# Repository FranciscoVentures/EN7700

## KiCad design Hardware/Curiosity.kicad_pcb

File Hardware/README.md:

Intro
=======

Curiosity™ EN7700
Developed by Francisco Ventures™

Based on the open source hardware project USB Armory MK II | https://github.com/f-secure-foundry/usbarmory/tree/master/hardware/mark-two

DISCLAIMER
=======

Francisco Ventures™ (“Francisco”) is not responsible for typographical or other errors or omissions or for direct, indirect, incidental or consequential damages related to this material or resulting from its use. Francisco makes no warranty or representation respecting this material, which is provided on an "AS IS" basis. FRANCISCO HEREBY DISCLAIMS ALL WARRANTIES OR LIABILITY OF ANY KIND WITH RESPECT THERETO, INCLUDING, WITHOUT LIMITATION, REPRESENTATIONS REGARDING ACCURACY AND COMPLETENESS, ALL IMPLIED WARRANTIES AND CONDITIONS OF MERCHANTABILITY, SUITABILITY OR FITNESS FOR A PARTICULAR PURPOSE, TITLE AND/OR NON-INFRINGEMENT. This material is not designed, intended or authorized for use in medical, life support, life sustaining or nuclear applications or applications in which the failure of the product could result in personal injury, death or property damage. Any party using or selling products for use in any such applications do so at their sole risk and agree that Francisco is not liable, in whole or in part, for any claim or damage arising from such use, and agree to fully indemnify, defend and hold harmless Francisco from and against any and all claims, damages, loss, cost, expense or liability arising out of or in connection with the use or performance of products in such applications.

License
=======

This is an open hardware design licensed under the terms of the CERN Open
Hardware Licence (OHL) v1.2.

You may redistribute and modify this documentation under the terms of the CERN
OHL v.1.2 (http://ohwr.org/cernohl). This documentation is distributed WITHOUT
ANY EXPRESS OR IMPLIED WARRANTY, INCLUDING OF MERCHANTABILITY, SATISFACTORY
QUALITY AND FITNESS FOR A PARTICULAR PURPOSE. Please see the CERN OHL v.1.2 for
applicable conditions.

The following exceptions apply:

- ../lib.snapeda: all files in this directory are imported or modified
from SnapEDA symbols and footprints, therefore the license at
https://www.snapeda.com/about/FAQ/#license applies.

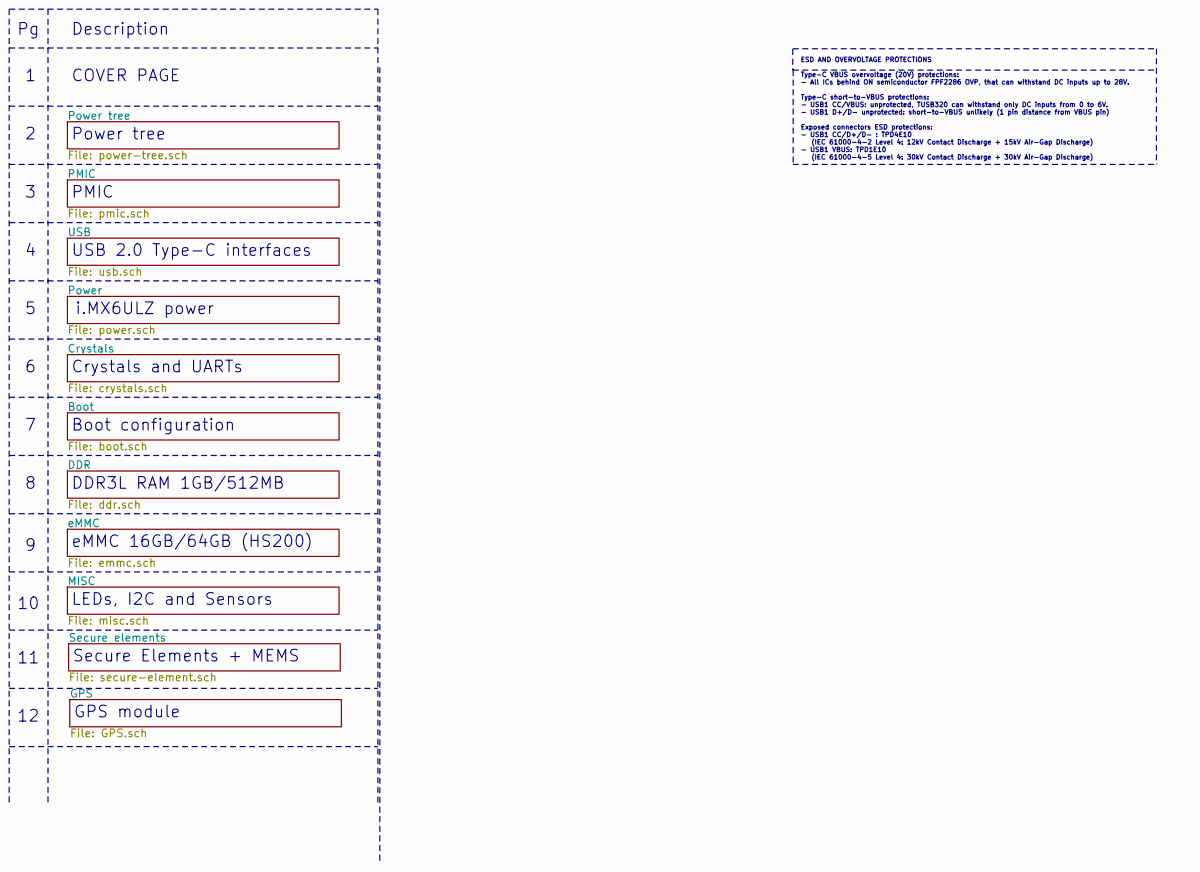
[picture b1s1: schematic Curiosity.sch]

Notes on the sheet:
DDR3L RAM 1GB/512MB
eMMC 16GB/64GB (HS200)
Secure Elements + MEMS
GPS module
Boot configuration
i.MX6ULZ power
USB 2.0 Type-C interfaces
Crystals and UARTs
ESD AND OVERVOLTAGE PROTECTIONS Type-C VBUS overvoltage (20V) protections: - All ICs behind ON semiconductor FPF2286 OVP, that can withstand DC inputs up to 28V. Type-C short-to-VBUS protections: - USB1 CC/VBUS: unprotected, TUSB320 can withstand only DC inputs from 0 to 6V. - USB1 D+/D- unprotecte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
PMIC
Description
Power tree
COVER PAGE
LEDs, I2C and Sensors

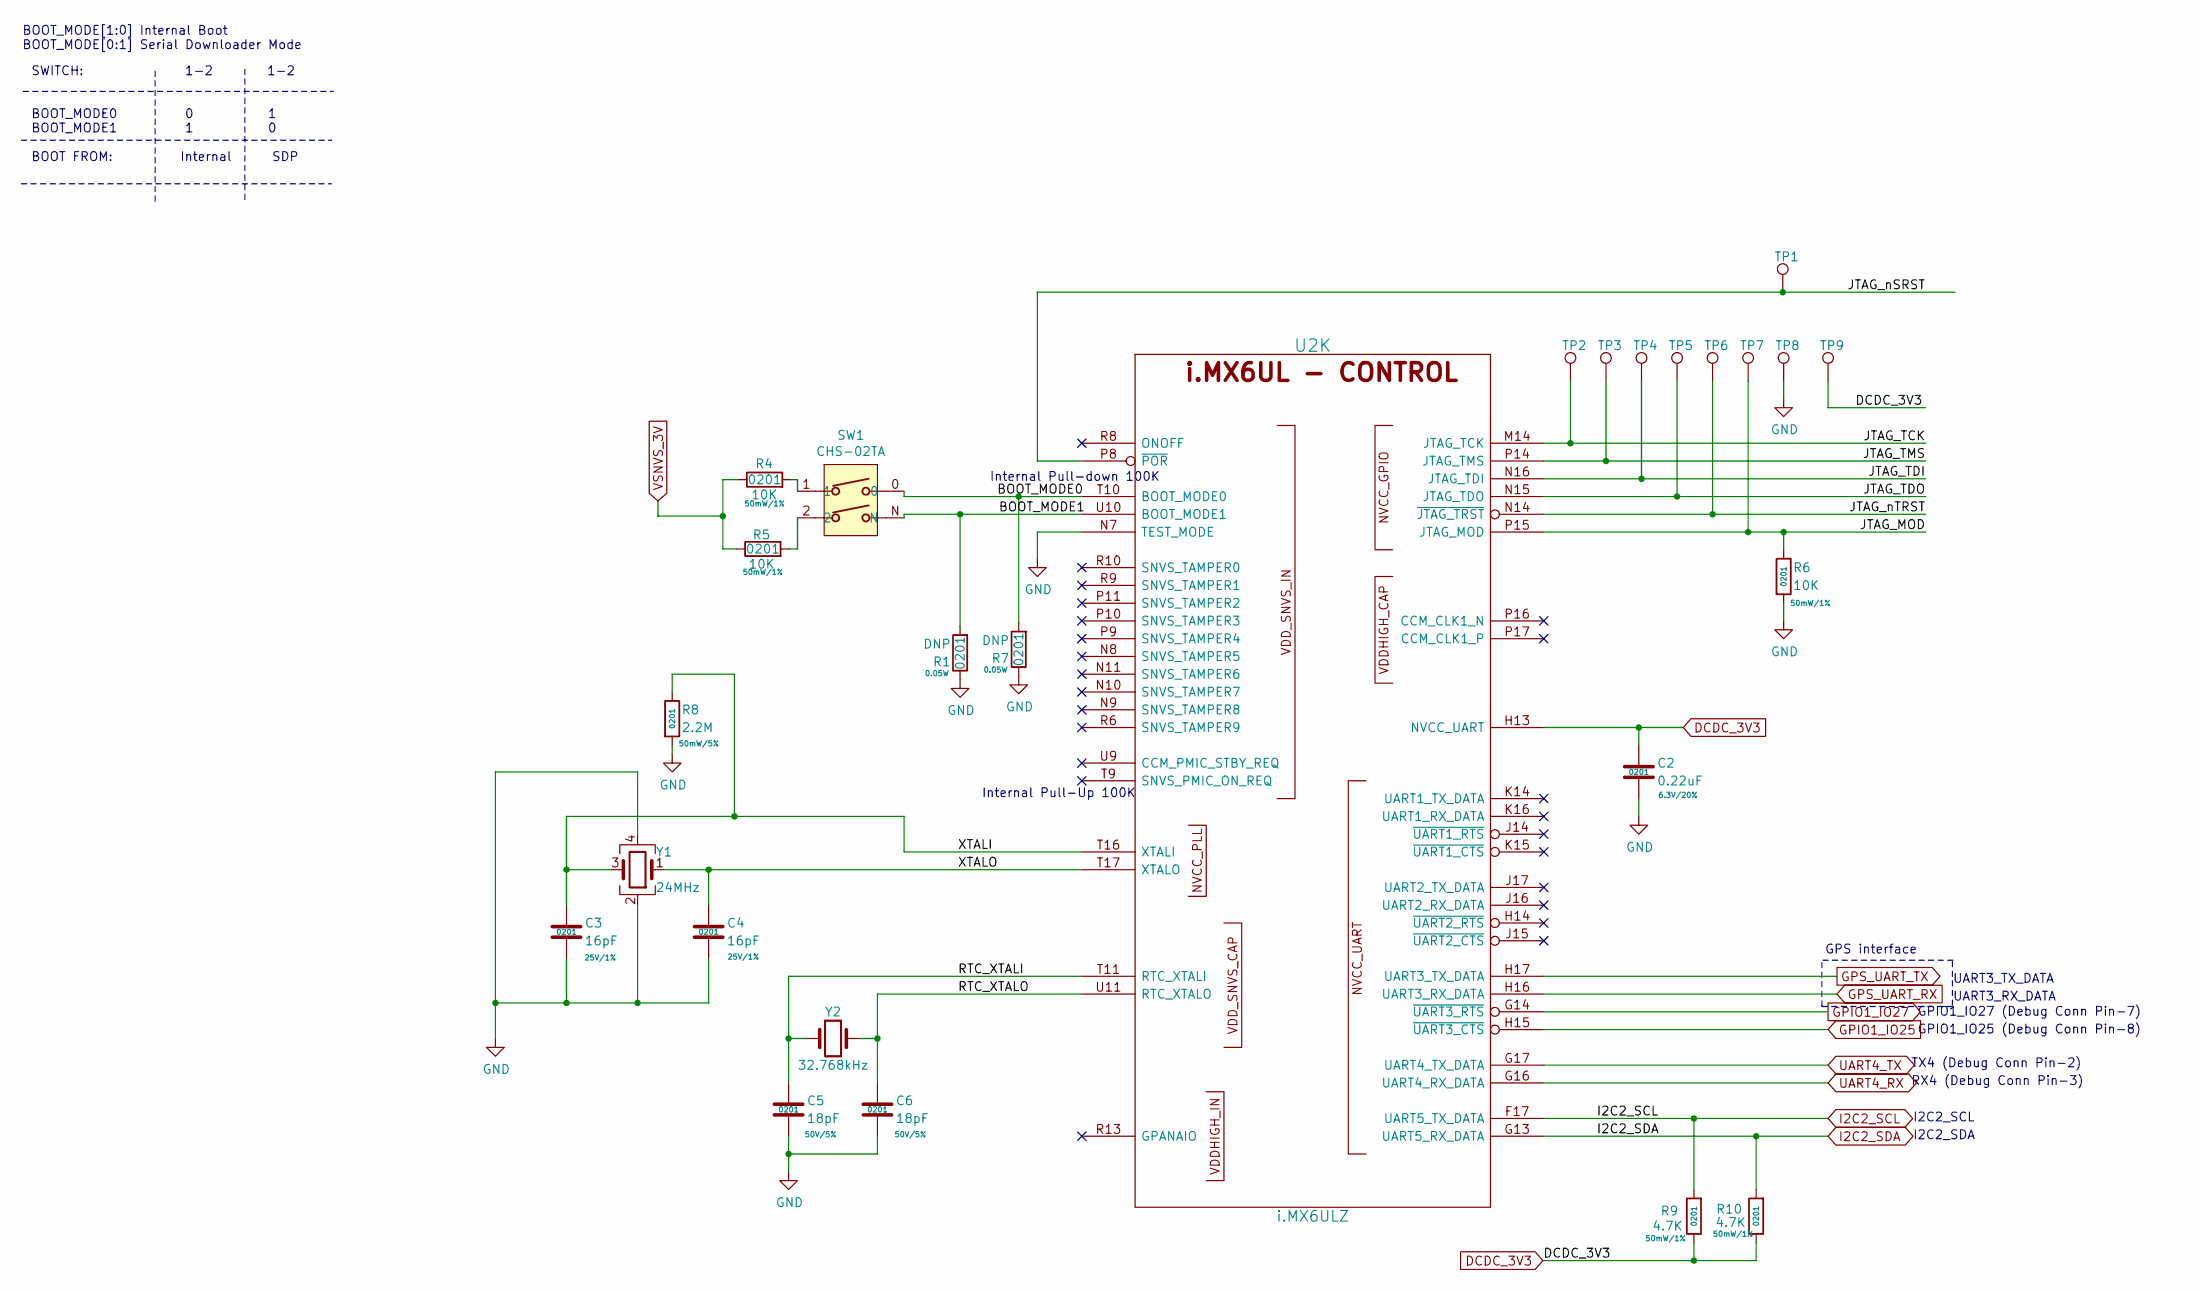
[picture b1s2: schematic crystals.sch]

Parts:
C2: 0.22uF; SM0201; Rating 6.3V/20%; Mfg PN GRM033R60J224ME15D; Digi-Key_PN 490-10407-1-ND
C3, C4: 16pF; SM0201; Rating 25V/1%; Mfg PN CBR02C160F3GAC; Digi-Key_PN 399-8574-1-ND
C5, C6: 18pF; SM0201; Rating 50V/5%; Mfg PN GRM0335C1H180JA01D; Digi-Key_PN 490-6117-1-ND
R1, R7: DNP; R_0201_0603Metric; Rating 0.05W; Mfg PN CRCW02010000Z0ED; Digi-Key_PN 541-0.0AGCT-ND
R4, R5, R6: 10K; R_0201_0603Metric; Rating 50mW/1%; Mfg PN CRCW020110K0JNED; Digi-Key_PN 541-10KAGCT-ND
R8: 2.2M; R_0201_0603Metric; Rating 50mW/5%; Mfg PN RC0201JR-072M2L; Digi-Key_PN YAG2882CT-ND
R9, R10: 4.7K; R_0201_0603Metric; Rating 50mW/1%; Mfg PN CRCW02014K70JNED; Digi-Key_PN 541-4.7KAGCT-ND
SW1: CHS-02TA; Mfg PN CHS-02TA; Digi-Key_PN 563-1005-2-ND
TP1, TP2, TP3, TP4, TP5, TP6, TP7, TP8, TP9: TestPoint; TP
U2: i.MX6ULZ; SOT1534-2; Mfg PN MCIMX6Z0DVM09AB; Digi-Key_PN 568-14726-ND
Y1: 24MHz; TSX-3225; Mfg PN TSX-3225 24.0000MF15X-AC3; Digi-Key_PN SER3635TR-ND
Y2: 32.768kHz; CM7V-T1A; Mfg PN CM7V-T1A-32.768KHZ-12.5PF-20PPM-TB-QA; Digi-Key_PN 2195-CM7V-T1A-32.768KHZ-12.5PF-20PPM-TB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

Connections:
/Crystals/BOOT_MODE0: R7.2, SW1.0, U2.T10 (BOOT_MODE0); also elsewhere on the board
/Crystals/BOOT_MODE1: R1.2, SW1.N, U2.U10 (BOOT_MODE1); also elsewhere on the board
/Crystals/JTAG_MOD: R6.1, TP7.1, U2.P15 (JTAG_MOD); also elsewhere on the board
/Crystals/JTAG_TCK: TP2.1, U2.M14 (JTAG_TCK); also elsewhere on the board
/Crystals/JTAG_TDI: TP4.1, U2.N16 (JTAG_TDI); also elsewhere on the board
/Crystals/JTAG_TDO: TP5.1, U2.N15 (JTAG_TDO); also elsewhere on the board
/Crystals/JTAG_TMS: TP3.1, U2.P14 (JTAG_TMS); also elsewhere on the board
/Crystals/JTAG_nSRST: TP1.1, U2.P8 (~POR); also elsewhere on the board
/Crystals/JTAG_nTRST: TP6.1, U2.N14 (~JTAG_TRST); also elsewhere on the board
/Crystals/RTC_XTALI: C5.1, U2.T11 (RTC_XTALI), Y2.1; also elsewhere on the board
/Crystals/RTC_XTALO: C6.1, U2.U11 (RTC_XTALO), Y2.2; also elsewhere on the board
/Crystals/XTALI: C3.1, R8.1, U2.T16 (XTALI), Y1.3; also elsewhere on the board
/Crystals/XTALO: C4.1, U2.T17 (XTALO), Y1.1; also elsewhere on the board
DCDC_3V3: C2.1, R9.1, R10.1, TP9.1, U2.H13 (NVCC_UART); also elsewhere on the board
GND: C2.2, C3.2, C4.2, C5.2, C6.2, R1.1, R6.2, R7.1, R8.2, TP8.1, U2.N7 (TEST_MODE), Y1.2, Y1.4; also elsewhere on the board
GPIO1_IO25: U2.H15 (~UART3_CTS); also elsewhere on the board
GPIO1_IO27: U2.G14 (~UART3_RTS); also elsewhere on the board
GPS_UART_RX: U2.H16 (UART3_RX_DATA); also elsewhere on the board
GPS_UART_TX: U2.H17 (UART3_TX_DATA); also elsewhere on the board
I2C2_SCL: R9.2, U2.F17 (UART5_TX_DATA); also elsewhere on the board
I2C2_SDA: R10.2, U2.G13 (UART5_RX_DATA); also elsewhere on the board
unnamed: R4.2, SW1.1
unnamed: R5.2, SW1.2
unnamed 213: U2.H14 (~UART2_RTS); also elsewhere on the board
unnamed 215: U2.J14 (~UART1_RTS); also elsewhere on the board
unnamed 216: U2.J15 (~UART2_CTS); also elsewhere on the board
unnamed 217: U2.J16 (UART2_RX_DATA); also elsewhere on the board
unnamed 218: U2.J17 (UART2_TX_DATA); also elsewhere on the board
unnamed 219: U2.K14 (UART1_TX_DATA); also elsewhere on the board
unnamed 220: U2.K15 (~UART1_CTS); also elsewhere on the board
unnamed 221: U2.K16 (UART1_RX_DATA); also elsewhere on the board
unnamed 222: U2.N8 (SNVS_TAMPER5); also elsewhere on the board
unnamed 223: U2.N9 (SNVS_TAMPER8); also elsewhere on the board
unnamed 224: U2.N10 (SNVS_TAMPER7); also elsewhere on the board
unnamed 225: U2.N11 (SNVS_TAMPER6); also elsewhere on the board
unnamed 226: U2.P9 (SNVS_TAMPER4); also elsewhere on the board
unnamed 227: U2.P10 (SNVS_TAMPER3); also elsewhere on the board
unnamed 228: U2.P11 (SNVS_TAMPER2); also elsewhere on the board
unnamed 229: U2.P16 (CCM_CLK1_N); also elsewhere on the board
unnamed 230: U2.P17 (CCM_CLK1_P); also elsewhere on the board
unnamed 231: U2.R6 (SNVS_TAMPER9); also elsewhere on the board
unnamed 232: U2.R8 (ONOFF); also elsewhere on the board
unnamed 233: U2.R9 (SNVS_TAMPER1); also elsewhere on the board
unnamed 234: U2.R10 (SNVS_TAMPER0); also elsewhere on the board
unnamed 235: U2.R13 (GPANAIO); also elsewhere on the board
unnamed 236: U2.T9 (SNVS_PMIC_ON_REQ); also elsewhere on the board
unnamed 238: U2.U9 (CCM_PMIC_STBY_REQ); also elsewhere on the board
UART4_RX: U2.G16 (UART4_RX_DATA); also elsewhere on the board
UART4_TX: U2.G17 (UART4_TX_DATA); also elsewhere on the board
VSNVS_3V: R4.1, R5.1; also elsewhere on the board

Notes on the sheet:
BOOT_MODE[1:0] Internal Boot BOOT_MODE[0:1] Serial Downloader Mode
GPS interface
UART3_TX_DATA
UART3_RX_DATA
SWITCH: 1-2 1-2 BOOT_MODE0 0 1 BOOT_MODE1 1 0 BOOT FROM: Internal SDP
GPIO1_IO27 (Debug Conn Pin-7)
RX4 (Debug Conn Pin-3)
TX4 (Debug Conn Pin-2)
I2C2_SDA
I2C2_SCL
Internal Pull-down 100K
Internal Pull-Up 100K
GPIO1_IO25 (Debug Conn Pin-8)

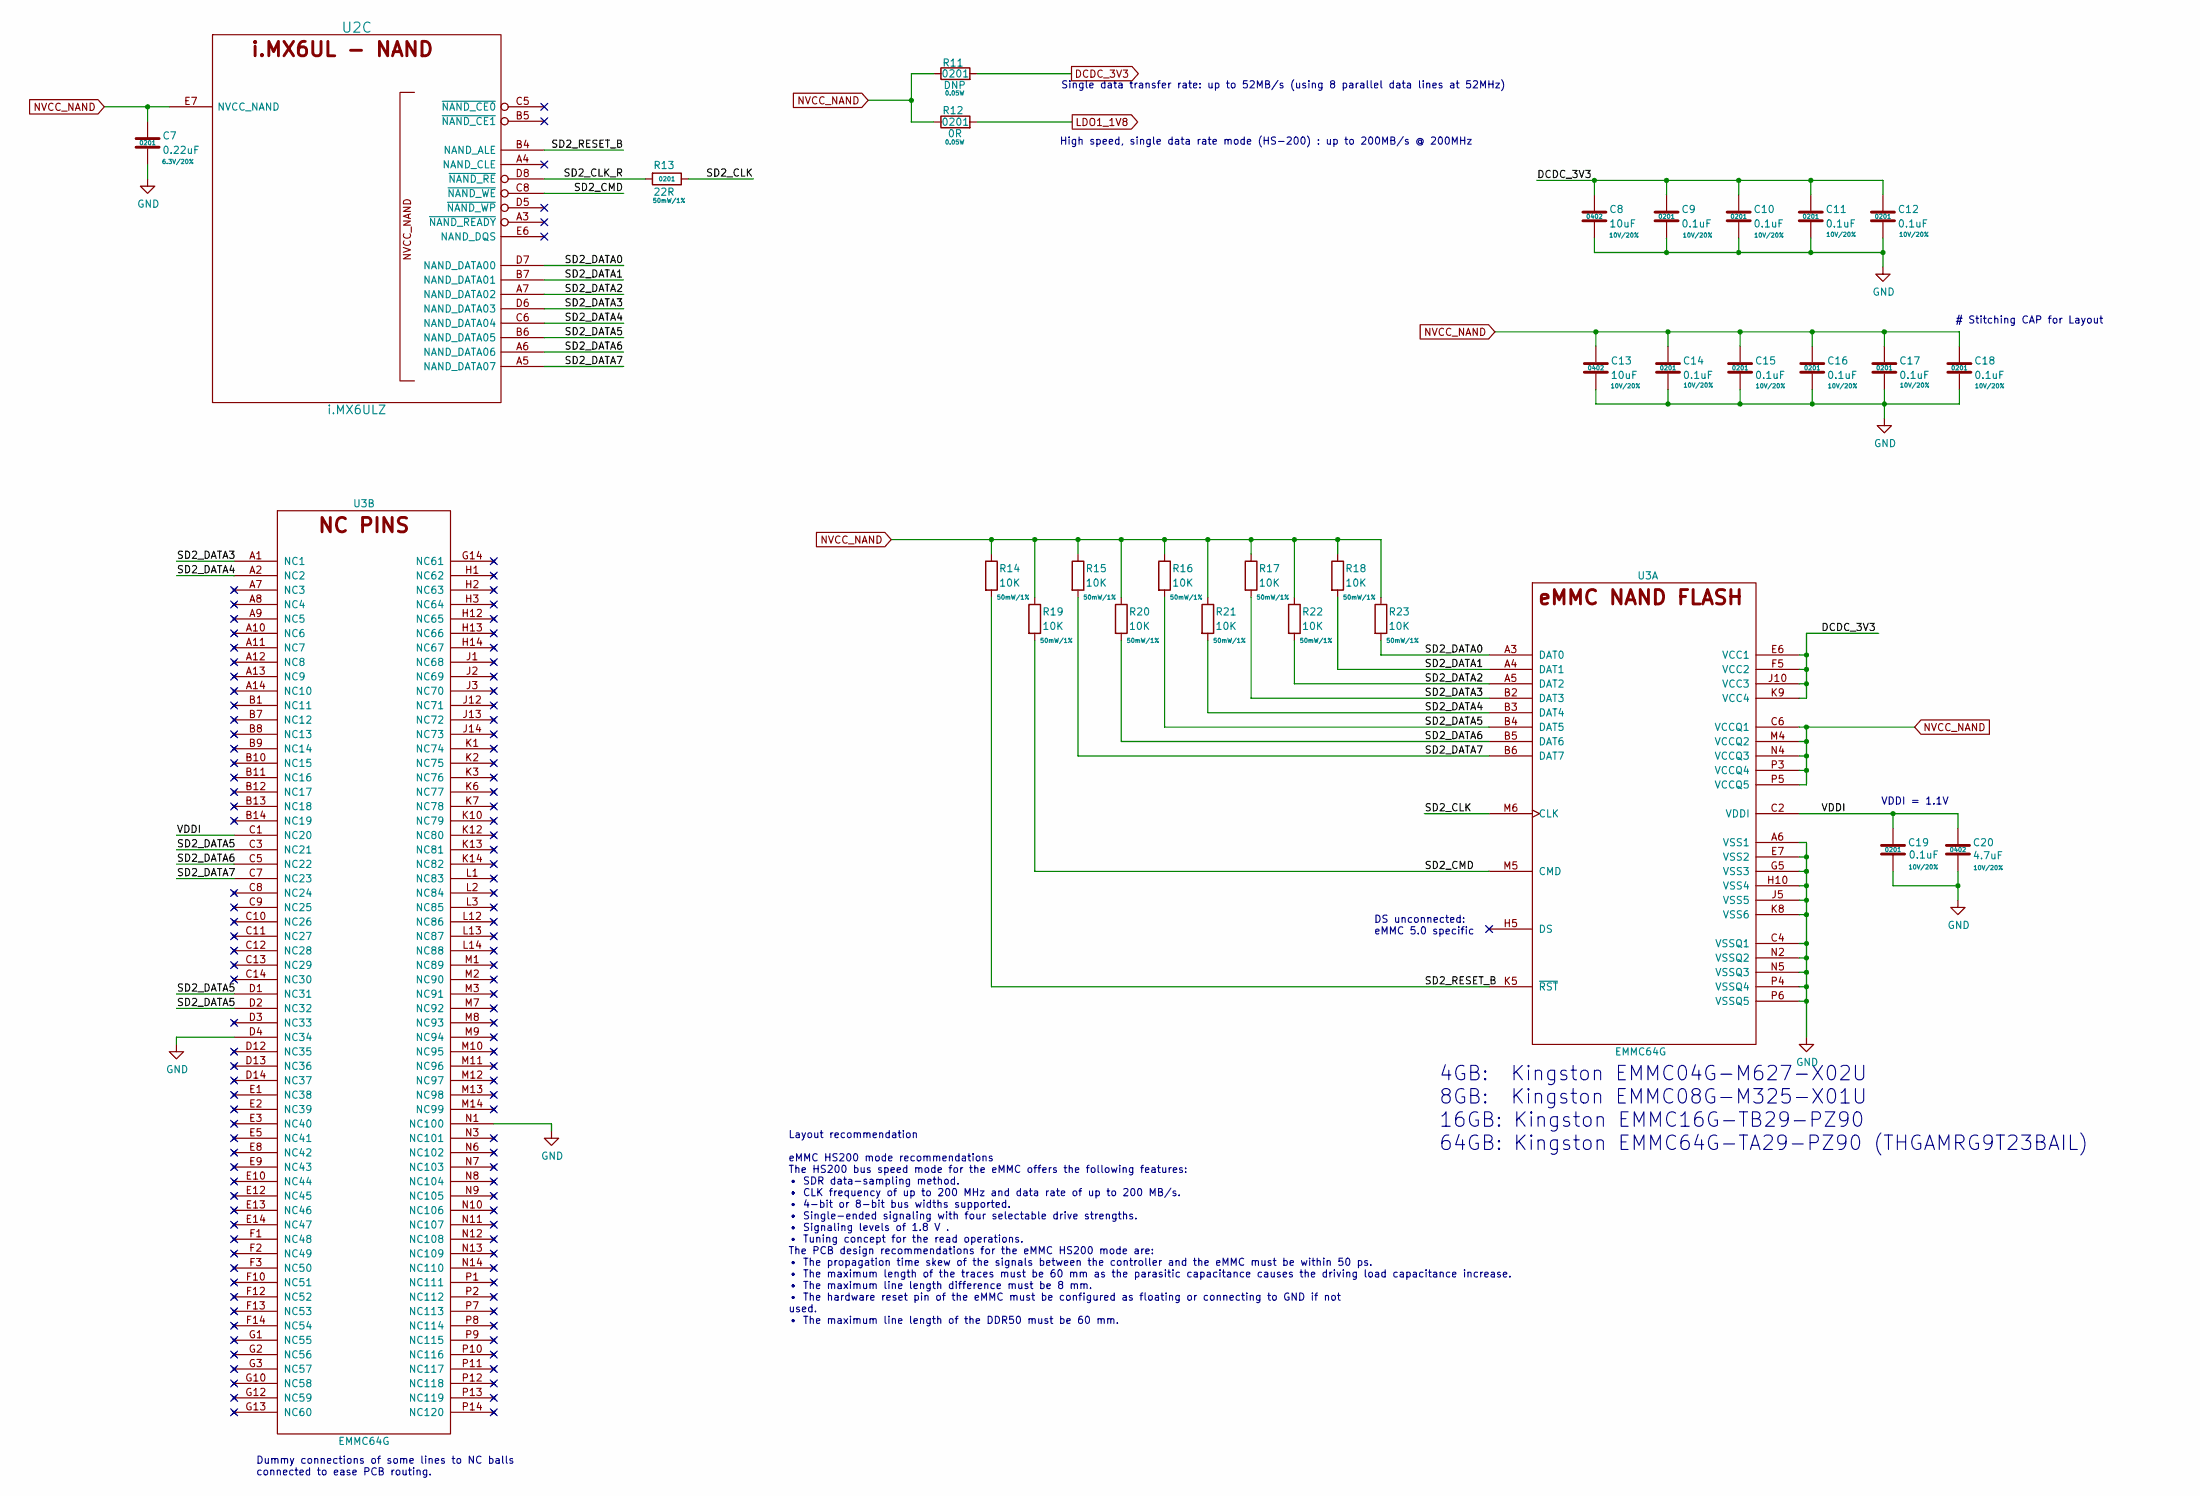
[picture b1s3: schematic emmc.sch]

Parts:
C7: 0.22uF; SM0201; Rating 6.3V/20%; Mfg PN GRM033R60J224ME15D; Digi-Key_PN 490-10407-1-ND
C8, C13: 10uF; SM0402; Rating 10V/20%; Mfg PN CL05A106MP8NUB8; Digi-Key_PN 1276-6830-1-ND
C9, C10, C11, C12, C14, C15, C16, C17, C18, C19: 0.1uF; SM0201; Rating 10V/20%; Mfg PN GRM033R61A104ME15D; Digi-Key_PN 490-5405-1-ND
C20: 4.7uF; SM0402; Rating 10V/20%; Mfg PN ZRB15XR61A475ME01D; Digi-Key_PN 490-10984-1-ND
R11: DNP; R_0201_0603Metric; Rating 0.05W; Mfg PN CRCW02010000Z0ED; Digi-Key_PN 541-0.0AGCT-ND
R12: 0R; R_0201_0603Metric; Rating 0.05W; Mfg PN CRCW02010000Z0ED; Digi-Key_PN 541-0.0AGCT-ND
R13: 22R; R_0201_0603Metric; Rating 50mW/1%; Mfg PN CRCW020122R0JNED; Digi-Key_PN 541-22AGCT-ND
R14, R15, R16, R17, R18, R19, R20, R21, R22, R23: 10K; R_0201_0603Metric; Rating 50mW/1%; Mfg PN CRCW020110K0JNED; Digi-Key_PN 541-10KAGCT-ND
U2: i.MX6ULZ; SOT1534-2; Mfg PN MCIMX6Z0DVM09AB; Digi-Key_PN 568-14726-ND
U3: EMMC64G; FBGA-153; Mfg PN THGAMRG9T23BAIL; Digi-Key_PN THGAMRG9T23BAIL-ND

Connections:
/eMMC/SD2_CLK: R13.1, U3.M6 (CLK)
/eMMC/SD2_CLK_R: R13.2, U2.D8 (~NAND_RE); also elsewhere on the board
/eMMC/SD2_CMD: R19.2, U2.C8 (~NAND_WE), U3.M5 (CMD); also elsewhere on the board
/eMMC/SD2_DATA0: R23.2, U2.D7 (NAND_DATA00), U3.A3 (DAT0); also elsewhere on the board
/eMMC/SD2_DATA1: R18.2, U2.B7 (NAND_DATA01), U3.A4 (DAT1); also elsewhere on the board
/eMMC/SD2_DATA2: R22.2, U2.A7 (NAND_DATA02), U3.A5 (DAT2); also elsewhere on the board
/eMMC/SD2_DATA3: R17.2, U2.D6 (NAND_DATA03), U3.A1 (NC1), U3.B2 (DAT3); also elsewhere on the board
/eMMC/SD2_DATA4: R21.2, U2.C6 (NAND_DATA04), U3.A2 (NC2), U3.B3 (DAT4); also elsewhere on the board
/eMMC/SD2_DATA5: R16.2, U2.B6 (NAND_DATA05), U3.B4 (DAT5), U3.C3 (NC21), U3.D1 (NC31), U3.D2 (NC32); also elsewhere on the board
/eMMC/SD2_DATA6: R20.2, U2.A6 (NAND_DATA06), U3.B5 (DAT6), U3.C5 (NC22); also elsewhere on the board
/eMMC/SD2_DATA7: R15.2, U2.A5 (NAND_DATA07), U3.B6 (DAT7), U3.C7 (NC23); also elsewhere on the board
/eMMC/SD2_RESET_B: R14.2, U2.B4 (NAND_ALE), U3.K5 (~RST); also elsewhere on the board
/eMMC/VDDI: C19.1, C20.1, U3.C1 (NC20), U3.C2 (VDDI)
DCDC_3V3: C8.1, C9.1, C10.1, C11.1, C12.1, R11.2, U3.E6 (VCC1), U3.F5 (VCC2), U3.J10 (VCC3), U3.K9 (VCC4); also elsewhere on the board
GND: C7.2, C8.2, C9.2, C10.2, C11.2, C12.2, C13.2, C14.2, C15.2, C16.2, C17.2, C18.2, C19.2, C20.2, U3.A6 (VSS1), U3.C4 (VSSQ1), U3.D4 (NC34), U3.E7 (VSS2), U3.G5 (VSS3), U3.H10 (VSS4), U3.J5 (VSS5), U3.K8 (VSS6), U3.N1 (NC100), U3.N2 (VSSQ2), U3.N5 (VSSQ3), U3.P4 (VSSQ4), U3.P6 (VSSQ5); also elsewhere on the board
LDO1_1V8: R12.2; also elsewhere on the board
NVCC_NAND: C7.1, C13.1, C14.1, C15.1, C16.1, C17.1, C18.1, R11.1, R12.1, R14.1, R15.1, R16.1, R17.1, R18.1, R19.1, R20.1, R21.1, R22.1, R23.1, U2.E7 (NVCC_NAND), U3.C6 (VCCQ1), U3.M4 (VCCQ2), U3.N4 (VCCQ3), U3.P3 (VCCQ4), U3.P5 (VCCQ5); also elsewhere on the board
unnamed 182: U2.A3 (~NAND_READY); also elsewhere on the board
unnamed 183: U2.A4 (NAND_CLE); also elsewhere on the board
unnamed 187: U2.B5 (~NAND_CE1); also elsewhere on the board
unnamed 191: U2.C5 (~NAND_CE0); also elsewhere on the board
unnamed 196: U2.D5 (~NAND_WP); also elsewhere on the board
unnamed 200: U2.E6 (NAND_DQS); also elsewhere on the board

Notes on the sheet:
Dummy connections of some lines to NC balls connected to ease PCB routing.
DS unconnected: eMMC 5.0 specific
4GB: Kingston EMMC04G-M627-X02U 8GB: Kingston EMMC08G-M325-X01U 16GB: Kingston EMMC16G-TB29-PZ90 64GB: Kingston EMMC64G-TA29-PZ90 (THGAMRG9T23BAIL)
# Stitching CAP for Layout
High speed, single data rate mode (HS-200) : up to 200MB/s @ 200MHz
Single data transfer rate: up to 52MB/s (using 8 parallel data lines at 52MHz)
Layout recommendation eMMC HS200 mode recommendations The HS200 bus speed mode for the eMMC offers the following features: • SDR data-sampling method. • CLK frequency of up to 200 MHz and data rate of up to 200 MB/s. • 4-bit or 8-bit bus widths supported. • Single-ended signaling with four selectab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
VDDI = 1.1V

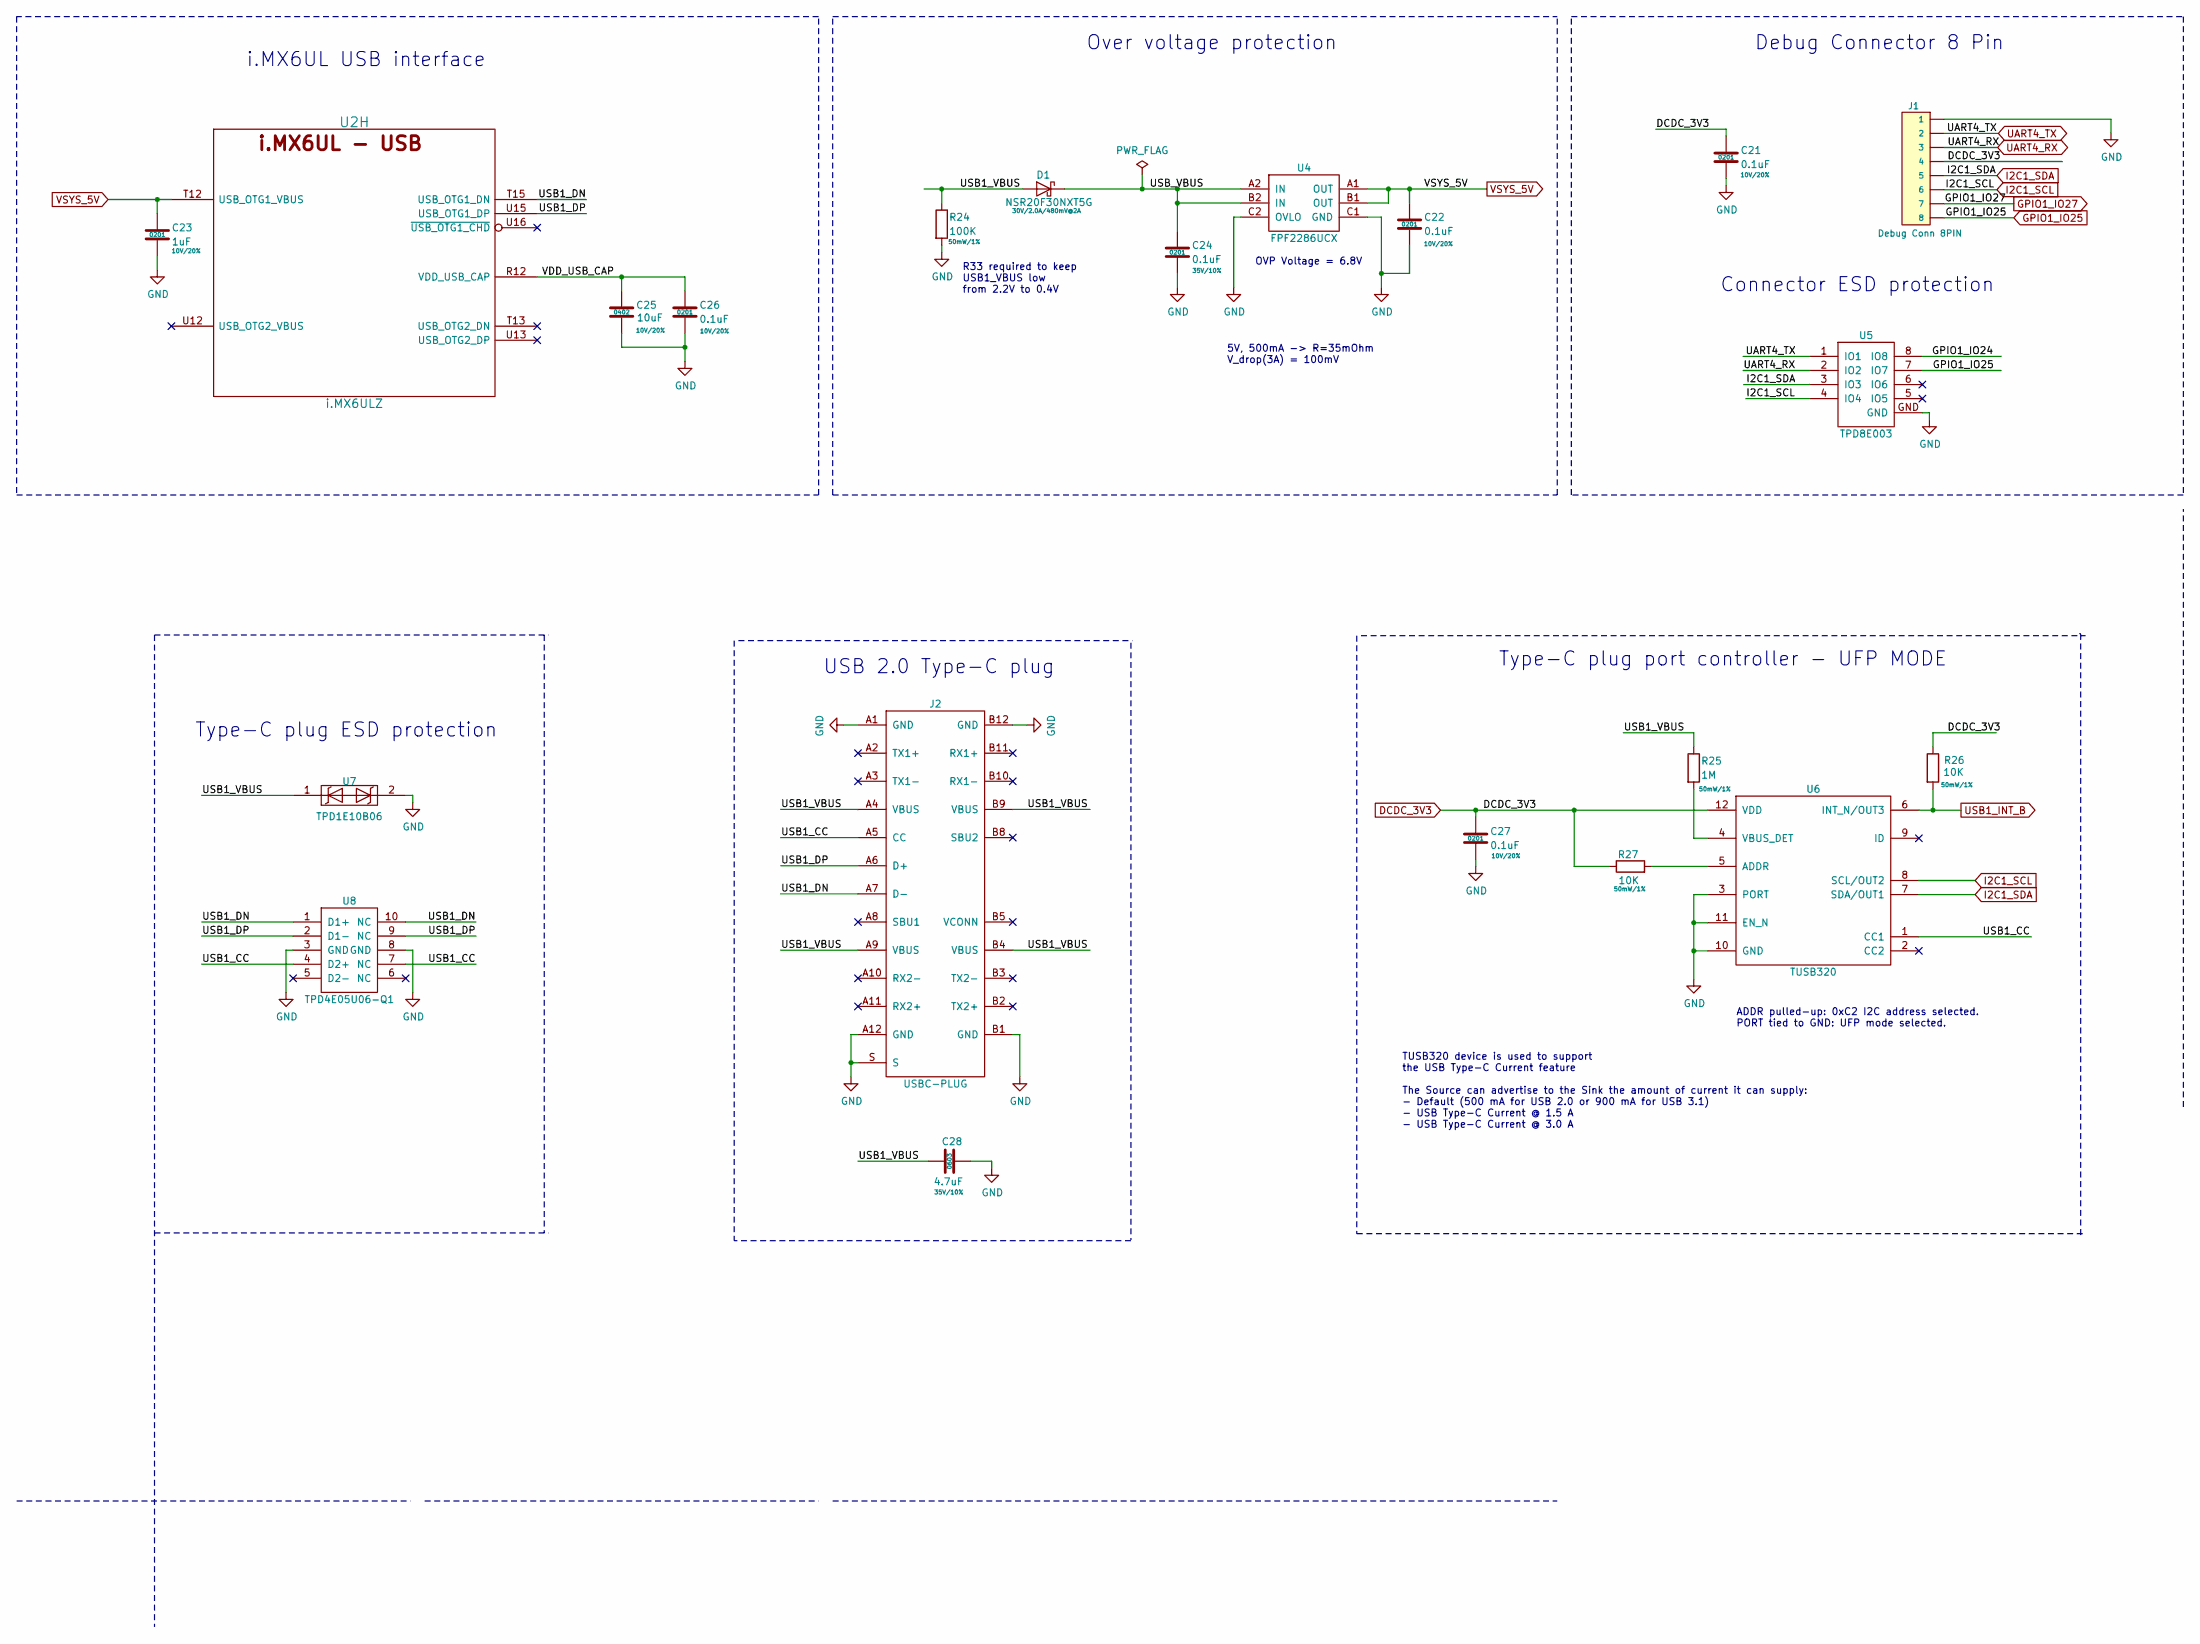
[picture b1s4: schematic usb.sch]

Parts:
C21, C22, C26, C27: 0.1uF; SM0201; Rating 10V/20%; Mfg PN GRM033R61A104ME15D; Digi-Key_PN 490-5405-1-ND
C23: 1uF; SM0201; Rating 10V/20%; Mfg PN CL03A105MP3ZSNH; Digi-Key_PN 1276-6816-1-ND
C24: 0.1uF; SM0201; Rating 35V/10%; Mfg PN GRM033R6YA104KE14D; Digi-Key_PN 490-10430-1-ND
C25: 10uF; SM0402; Rating 10V/20%; Mfg PN CL05A106MP8NUB8; Digi-Key_PN 1276-6830-1-ND
C28: 4.7uF; SM0603; Rating 35V/10%; Mfg PN GRM188R6YA475KE15D; Digi-Key_PN 490-7205-1-ND
D1: NSR20F30NXT5G; DSN2; Rating 30V/2.0A/480mV@2A; Mfg PN NSR20F30NXT5G; Digi-Key_PN NSR20F30NXT5GOSCT-ND
J1: Debug Conn 8PIN; BC075-08; Mfg PN BC075-08-A-L-A; Digi-Key_PN 2073-BC075-08-A-L-ACT-ND
J2: USBC-PLUG; WURTH_632712000011; Mfg PN 632712000011; Digi-Key_PN 732-9616-1-ND
R24: 100K; R_0201_0603Metric; Rating 50mW/1%; Mfg PN CRCW0201100KJNED; Digi-Key_PN 541-100KAGCT-ND
R25: 1M; R_0201_0603Metric; Rating 50mW/1%; Mfg PN CRCW02011M00FKED; Digi-Key_PN 541-1.00MAABCT-ND
R26, R27: 10K; R_0201_0603Metric; Rating 50mW/1%; Mfg PN CRCW020110K0JNED; Digi-Key_PN 541-10KAGCT-ND
U2: i.MX6ULZ; SOT1534-2; Mfg PN MCIMX6Z0DVM09AB; Digi-Key_PN 568-14726-ND
U4: FPF2286UCX; WLCSP-6; Mfg PN FPF2286UCX; Digi-Key_PN FPF2286UCXOSCT-ND
U5: TPD8E003; WSON-8; Mfg PN TPD8E003DQDR; Digi-Key_PN 296-27669-1-ND
U6: TUSB320; RWB-QFN-12; Mfg PN TUSB320IRWBR; Digi-Key_PN 296-42175-1-ND
U7: TPD1E10B06; X1SON-2; Mfg PN TPD1E10B06DPYR; Digi-Key_PN 296-30406-1-ND
U8: TPD4E05U06-Q1; DQA-USON-10; Mfg PN TPD4E05U06DQAR; Digi-Key_PN 296-35765-1-ND

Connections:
/USB/USB1_CC: J2.A5 (CC), U6.1 (CC1), U8.4 (D2+), U8.7 (NC)
/USB/USB1_DN: J2.A7 (D-), U2.T15 (USB_OTG1_DN), U8.1 (D1+), U8.10 (NC); also elsewhere on the board
/USB/USB1_DP: J2.A6 (D+), U2.U15 (USB_OTG1_DP), U8.2 (D1-), U8.9 (NC); also elsewhere on the board
/USB/USB1_VBUS: C28.1, D1.2 (A), J2.A4 (VBUS), J2.A9 (VBUS), J2.B4 (VBUS), J2.B9 (VBUS), R24.1, R25.1, U7.1
/USB/USB_VBUS: C24.1, D1.1 (K), U4.A2 (IN), U4.B2 (IN)
/USB/VDD_USB_CAP: C25.1, C26.1, U2.R12 (VDD_USB_CAP); also elsewhere on the board
DCDC_3V3: C21.1, C27.1, J1.4, R26.1, R27.1, U6.12 (VDD); also elsewhere on the board
GND: C21.2, C22.2, C23.2, C24.2, C25.2, C26.2, C27.2, C28.2, J1.1, J2.A1 (GND), J2.A12 (GND), J2.B1 (GND), J2.B12 (GND), J2.S, R24.2, U4.C1 (GND), U4.C2 (OVLO), U5.GND, U6.3 (PORT), U6.10 (GND), U6.11 (EN_N), U7.2, U8.3 (GND), U8.8 (GND); also elsewhere on the board
GPIO1_IO25: J1.8, U5.7 (IO7); also elsewhere on the board
GPIO1_IO27: J1.7; also elsewhere on the board
I2C1_SCL: J1.6, U5.4 (IO4), U6.8 (SCL/OUT2); also elsewhere on the board
I2C1_SDA: J1.5, U5.3 (IO3), U6.7 (SDA/OUT1); also elsewhere on the board
unnamed: R25.2, U6.4 (VBUS_DET)
unnamed: R27.2, U6.5 (ADDR)
unnamed 237: U2.T13 (USB_OTG2_DN); also elsewhere on the board
unnamed 239: U2.U12 (USB_OTG2_VBUS); also elsewhere on the board
unnamed 240: U2.U13 (USB_OTG2_DP); also elsewhere on the board
unnamed 241: U2.U16 (~USB_OTG1_CHD); also elsewhere on the board
UART4_RX: J1.3, U5.2 (IO2); also elsewhere on the board
UART4_TX: J1.2, U5.1 (IO1); also elsewhere on the board
USB1_INT_B: R26.2, U6.6 (INT_N/OUT3); also elsewhere on the board
VSYS_5V: C22.1, C23.1, U2.T12 (USB_OTG1_VBUS), U4.A1 (OUT), U4.B1 (OUT); also elsewhere on the board

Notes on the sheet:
ADDR pulled-up: 0xC2 I2C address selected. PORT tied to GND: UFP mode selected.
TUSB320 device is used to support the USB Type-C Current feature The Source can advertise to the Sink the amount of current it can supply: - Default (500 mA for USB 2.0 or 900 mA for USB 3.1) - USB Type-C Current @ 1.5 A - USB Type-C Current @ 3.0 A
USB 2.0 Type-C plug
Type-C plug ESD protection
Connector ESD protection
Type-C plug port controller - UFP MODE
OVP Voltage = 6.8V
5V, 500mA -> R=35mOhm V_drop(3A) = 100mV
Over voltage protection
i.MX6UL USB interface
R33 required to keep USB1_VBUS low from 2.2V to 0.4V
Debug Connector 8 Pin

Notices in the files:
Hardware/Curiosity.kicad_pcb:
Copyright © Francisco Ventures
License: CERN OHL v1.2
Hardware/Curiosity.sch:
Copyright © 2019 F-Secure
parts and their libraries:
Copyright 2016 Accelerated Designs. All rights reserved.
